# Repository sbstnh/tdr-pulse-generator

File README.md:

# TDR pulse generator

This repository contains the PCB design files (KiCAD 8) of a simple TDR pulse generator.

## Introduction

Almost a decade ago W2AEW posted a video on his YouTube channel showing a cheap and easy to build pulse generator for time domain reflectometry (TDR), consisting of only a simple hex inverter with schmitt-trigger inputs 74AC14 and a few passive components.
The schematic looks something like this:

It consists of a schmitt-trigger oscillator and a few inverters used as a driver with a (somewhat) fast rise time.

This repository contains an implementation of such a circuit.

## Results

For the test I used my Siglent SDS2000X Plus scope (500MHz, 800ps rise time typical @ 50 Ohm) which has to stretch its legs for this one: I measured a respectable rise time of about 960ps.
In his video, W2AEW measured something like 2ns of rise time for his circuit using DIP packaged hex inverter. Both his and my variant show a noticable ringing.

## Credits

Circuit presented by W2AEW on his youtube channel. The video can be found here: [https://www.youtube.com/watch?v=9cP6w2odGUc](https://www.youtube.com/watch?v=9cP6w2odGUc).

## Further information

More details are available on my personal site [https://sebastianharnisch.de](https://sebastianharnisch.de).

## Disclaimer

This repository all its Content is provided "AS IS" without any warranty whatsoever.

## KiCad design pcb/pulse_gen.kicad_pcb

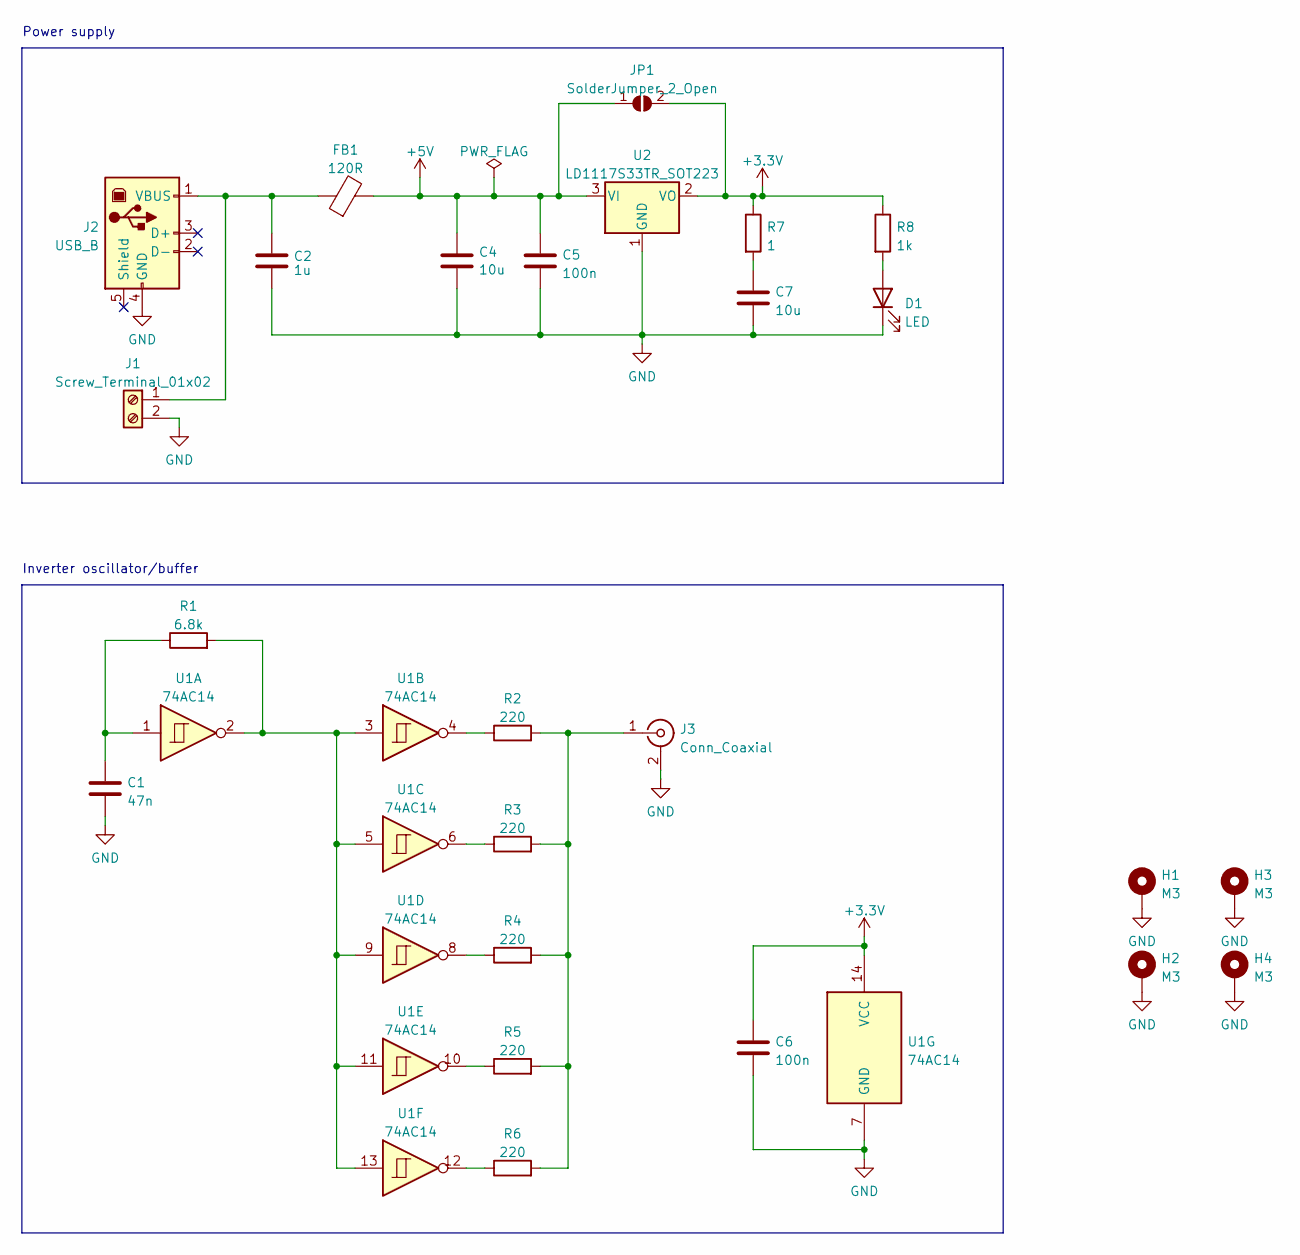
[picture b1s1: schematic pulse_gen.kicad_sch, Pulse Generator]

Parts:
C1: 47n; C_0805_2012Metric
C2: 1u; C_0805_2012Metric
C4: 10u; C_1206_3216Metric
C5, C6: 100n; C_0805_2012Metric
C7: 10u; C_0805_2012Metric
D1: LED; LED_0805_2012Metric
FB1: 120R; L_0805_2012Metric
H1, H2, H3, H4: M3; MountingHole_3.2mm_M3_DIN965_Pad
J1: Screw_Terminal_01x02; PhoenixContact_MSTBA_2,5_2-G_1x02_P5.00mm_Horizontal
J2: USB_B; USB_B_Lumberg_2411_02_Horizontal
J3: Conn_Coaxial; BNC_Amphenol_B6252HB-NPP3G-50_Horizontal
JP1: SolderJumper_2_Open; SolderJumper-2_P1.3mm_Open_RoundedPad1.0x1.5mm
R1: 6.8k; R_0805_2012Metric
R2, R3, R4, R5, R6: 220; R_0805_2012Metric
R7: 1; R_0805_2012Metric
R8: 1k; R_0805_2012Metric
U1: 74AC14; SOIC-14_3.9x8.7mm_P1.27mm
U2: LD1117S33TR_SOT223; SOT-223-3_TabPin2

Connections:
+3.3V: C6.1, JP1.2 (B), R7.1, R8.1, U1.14 (VCC), U2.2 (VO)
+5V: C4.1, C5.1, FB1.2, JP1.1 (A), U2.3 (VI)
GND: C1.2, C2.2, C4.2, C5.2, C6.2, C7.2, D1.1 (K), H1.1, H2.1, H3.1, H4.1, J1.2, J2.4 (GND), J3.2 (Ext), U1.7 (GND), U2.1 (GND)
unnamed: C1.1, R1.1, U1.1
unnamed: C7.1, R7.2
unnamed: D1.2 (A), R8.2
unnamed: C2.1, FB1.1, J1.1, J2.1 (VBUS)
unnamed: J3.1 (In), R2.2, R3.2, R4.2, R5.2, R6.2
unnamed: R1.2, U1.2, U1.3, U1.5, U1.9, U1.11, U1.13
unnamed: R2.1, U1.4
unnamed: R3.1, U1.6
unnamed: R4.1, U1.8
unnamed: R5.1, U1.10
unnamed: R6.1, U1.12

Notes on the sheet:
Power supply
Inverter oscillator/buffer

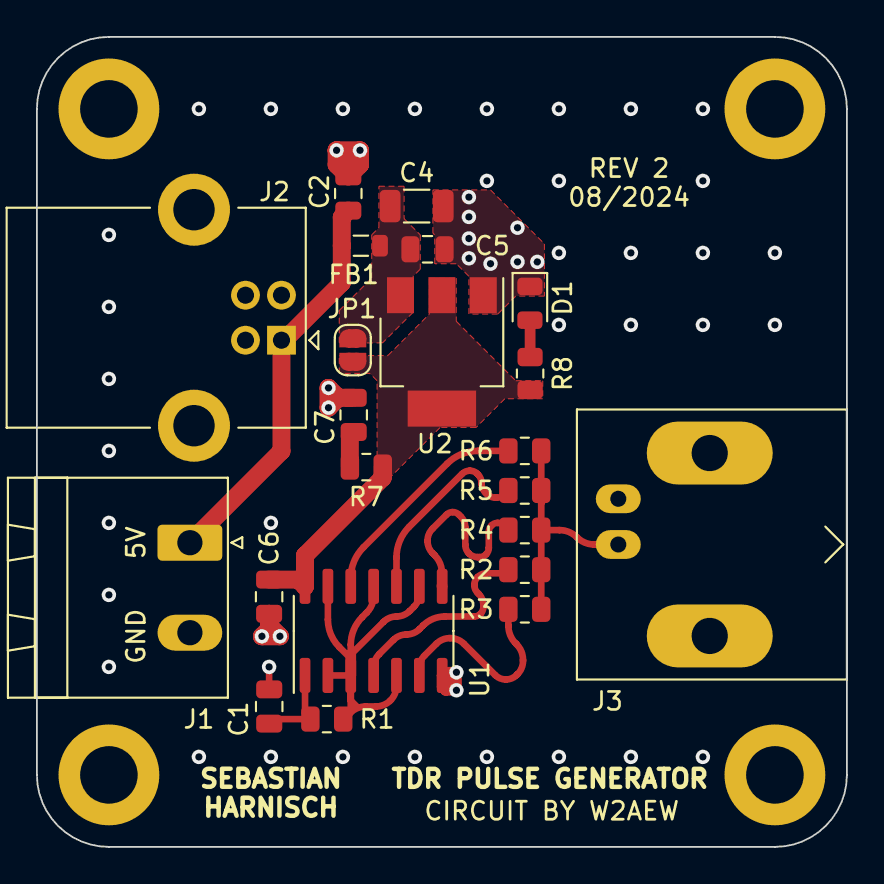
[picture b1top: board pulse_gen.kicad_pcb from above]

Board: 4 copper layers, 45.0 x 45.0 mm, 26 parts (0 on the bottom side), 14 nets.

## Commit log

2025-05-05 Update to KiCAD v9 etc.
